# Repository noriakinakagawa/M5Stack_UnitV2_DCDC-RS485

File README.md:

# M5Stack_UnitV2_DCDC-RS485
M5Stack UnitV2とコマンドサーボをRS485経由で直結できるモジュール。
ただし、半導体不足によりいくつかの部品は秋月電子部品で購入した同等品で動作確認を行っています。

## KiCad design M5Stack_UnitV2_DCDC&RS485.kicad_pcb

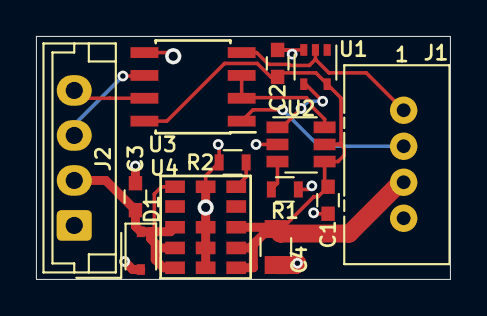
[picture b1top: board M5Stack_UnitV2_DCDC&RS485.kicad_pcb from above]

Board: 2 copper layers, 23.0 x 13.5 mm, 13 parts (0 on the bottom side), 11 nets.

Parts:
C1, C2, C3: 0.1u; C_0603
C4: 22u; C_0805
D1: 15V; D_SOD-323
J1: Grove_1x04
J2: B4B-EH; JST_EH_B4B-EH-A_1x04_P2.50mm_Vertical
R1: 470k; R_0603
R2: 130; R_0603
U1: 74LVC1G04; SOT-353_SC-70-5
U2: LTC6994xS6-1; TSOT-23-6
U3: ST1480ACDR; SOIC-8_3.9x4.9mm_Pitch1.27mm
U4: LXDC55F; LXDC55FAAA-203

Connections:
+5V: C1.1, C2.1, C4.1, J1.3, U1.5, U2.4, U2.5, U3.8, U4.7, U4.8, U4.9
+12V: C3.1, D1.1, J2.2, U4.1, U4.3, U4.4, U4.5
GND: C1.2, C2.2, C3.2, C4.2, D1.2, J1.4, J2.1, R1.2, R2.2, U1.3, U2.2, U3.5, U4.6, U4.12, U4.13, U4.14
unnamed: J2.3, U3.6
unnamed: J2.4, U3.7
unnamed: R1.1, U2.3
unnamed: R2.1, U4.11
unnamed: U1.4, U2.1
unnamed: U2.6, U3.2, U3.3
RXD: J1.2, U3.1
TXD: J1.1, U1.2, U3.4

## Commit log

2022-01-30 Create README.md
    Create README.md
